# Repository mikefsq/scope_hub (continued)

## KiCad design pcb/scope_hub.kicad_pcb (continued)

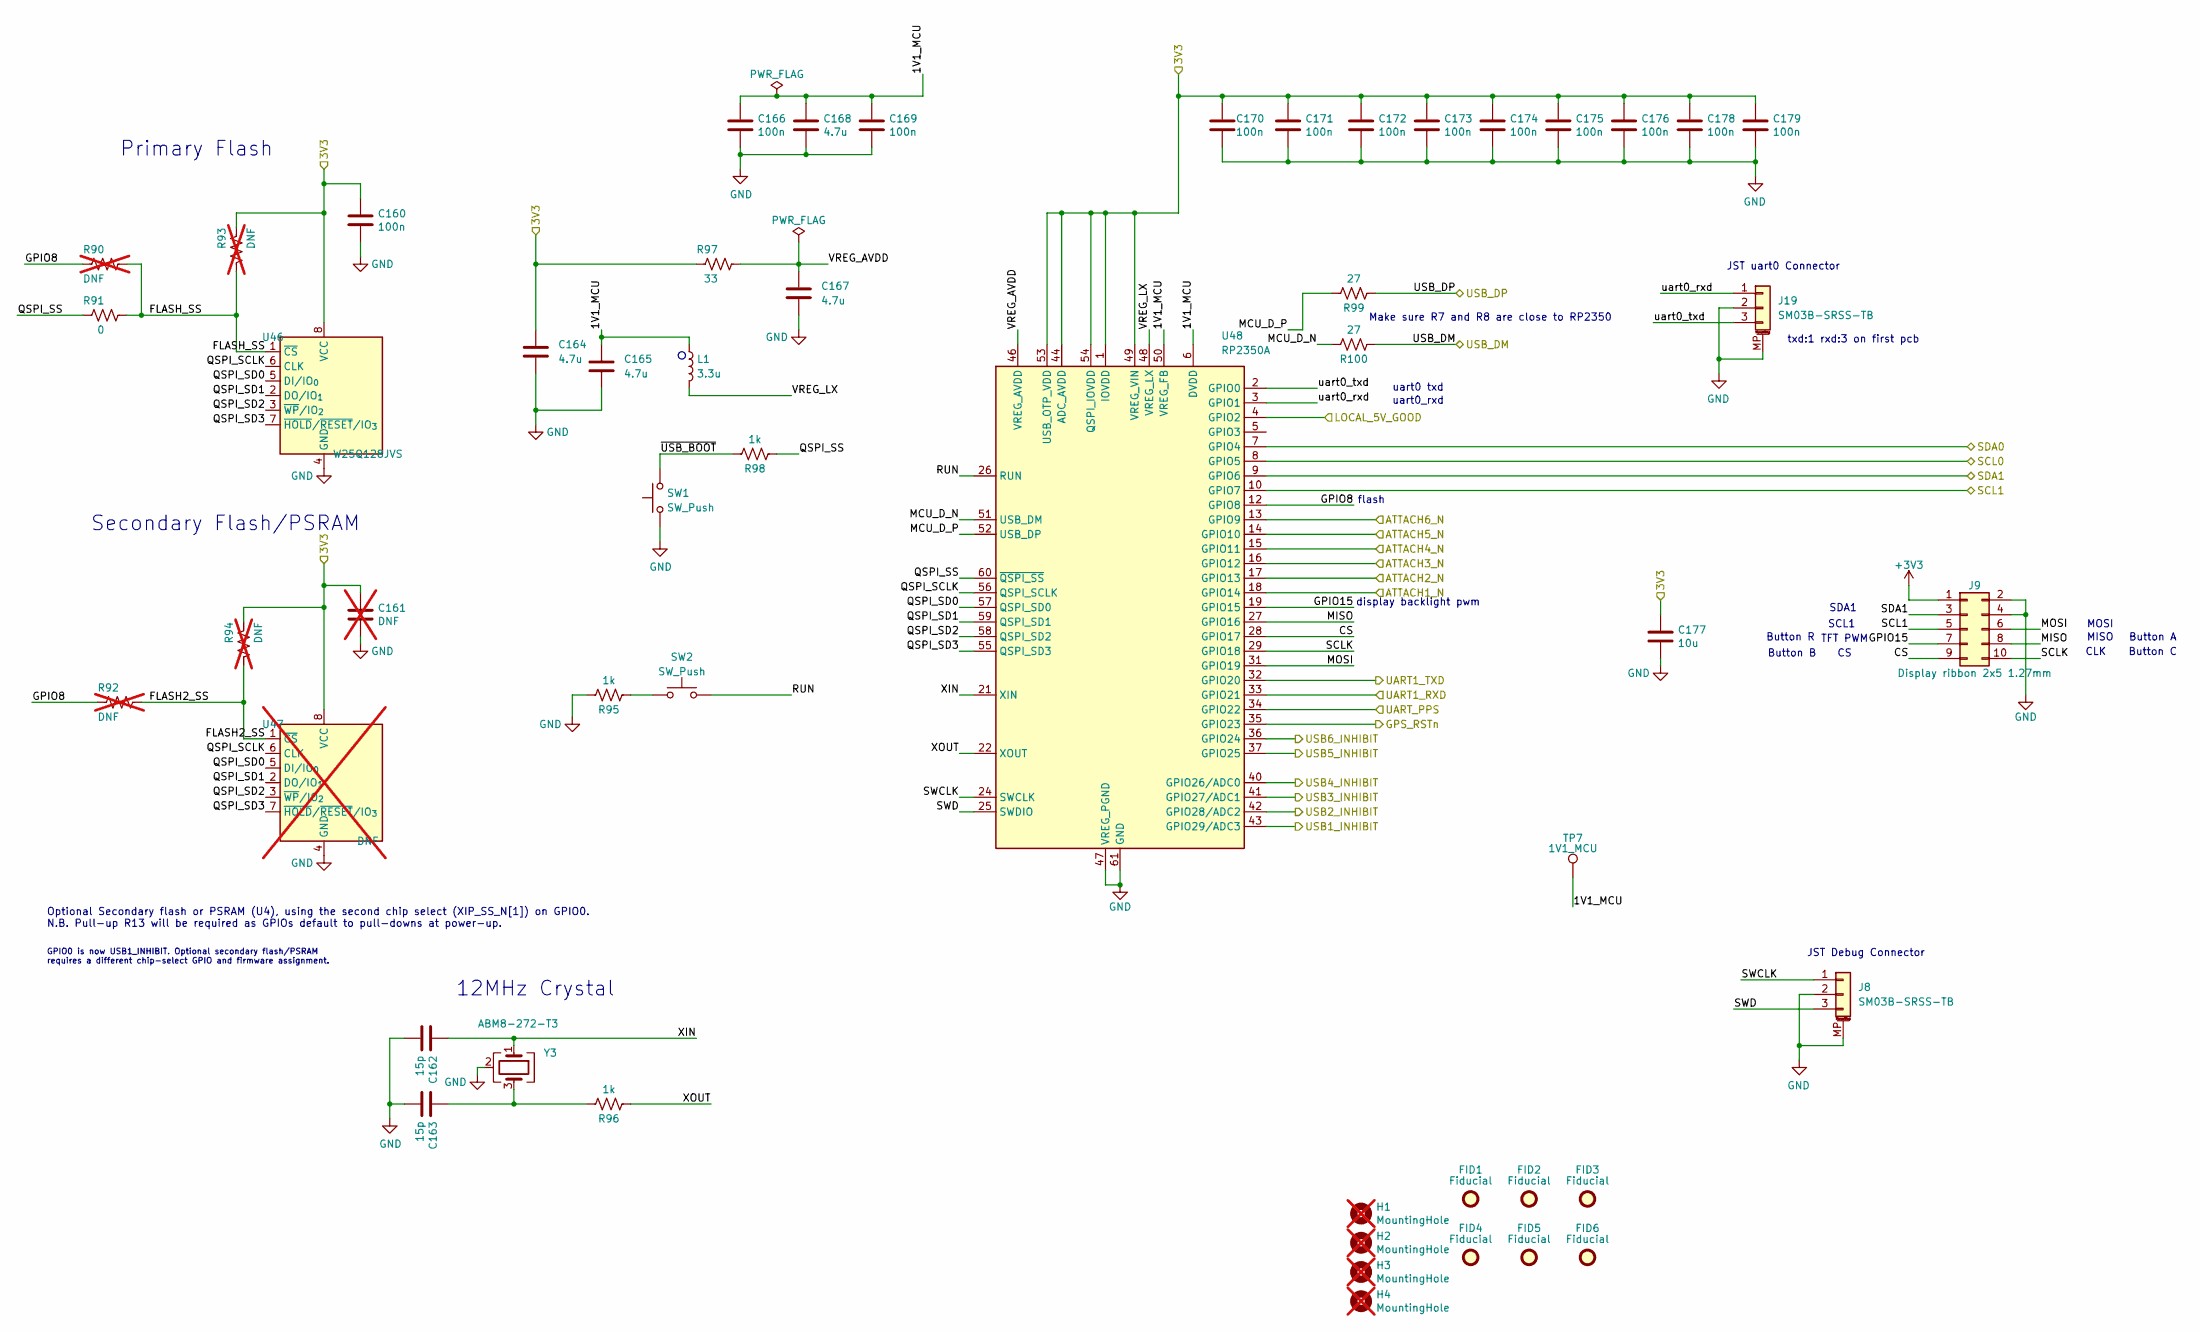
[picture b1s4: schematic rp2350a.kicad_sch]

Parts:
C160, C166, C169, C170, C171, C172, C173, C174, C175, C176, C178, C179: 100n; C_0402_1005Metric; LCSC C1525
C161: DNF; C_0402_1005Metric; not fitted
C162, C163: 15p; C_0402_1005Metric; LCSC C1548
C164, C165, C167, C168: 4.7u; C_0402_1005Metric; LCSC C23733
C177: 10u; C_0805_2012Metric; LCSC C15850
FID1, FID2, FID3, FID4, FID5, FID6: Fiducial; Fiducial_1mm_Mask3mm
H1, H2, H3, H4: MountingHole; MountingHole_3.2mm_M3; not fitted
J8, J19: SM03B-SRSS-TB; JST_SH_SM03B-SRSS-TB_1x03-1MP_P1.00mm_Horizontal; MPN SM03B-SRSS-TB(LF)(SN); LCSC C160403
J9: Display ribbon 2x5 1.27mm; PinHeader_2x05_P1.27mm_Vertical_SMD; MPN FTSH-105-01-L-DV-K-TR; LCSC C448647
L1: 3.3u; L_pol_2016; MPN AOTA-B201610S3R3-101-T; LCSC C42411119
R90, R92, R93, R94: DNF; R_0402_1005Metric; not fitted
R91: 0; R_0402_1005Metric; LCSC C17168
R95, R96, R98: 1k; R_0402_1005Metric; LCSC C11702
R97: 33; R_0402_1005Metric; LCSC C25105
R99, R100: 27; R_0402_1005Metric; LCSC C25100
SW1, SW2: SW_Push; SW_Push_1P1T_NO_Vertical_Wuerth_434133025816; MPN 434133025816; LCSC C5504987
TP7: 1V1_MCU; TestPoint_Pad_D1.5mm
U46: W25Q128JVS; SOIC-8_5.3x5.3mm_P1.27mm; MPN W25Q128JVSIQ; LCSC C97521
U47: DNF; SOIC-8_5.3x5.3mm_P1.27mm; not fitted
U48: RP2350A; QFN-60-1EP_7x7mm_P0.4mm_EP3.4x3.4mm_ThermalVias; LCSC C42411118
Y3: ABM8-272-T3; Crystal_SMD_3225-4Pin_3.2x2.5mm; MPN ABM8-272-T3; LCSC C20625731

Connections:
+3V3: C160.1, C161.1, C164.1, C170.1, C171.1, C172.1, C173.1, C174.1, C175.1, C176.1, C177.1, C178.1, C179.1, J9.1, R93.1, R94.1, R97.1, U46.8 (VCC), U47.8 (VCC), U48.1 (IOVDD), U48.11 (IOVDD), U48.20 (IOVDD), U48.30 (IOVDD), U48.38 (IOVDD), U48.44 (ADC_AVDD), U48.45 (IOVDD), U48.49 (VREG_VIN), U48.53 (USB_OTP_VDD), U48.54 (QSPI_IOVDD); also elsewhere on the board
/ATTACH1_N: U48.18 (GPIO14); also elsewhere on the board
/ATTACH2_N: U48.17 (GPIO13); also elsewhere on the board
/ATTACH3_N: U48.16 (GPIO12); also elsewhere on the board
/ATTACH4_N: U48.15 (GPIO11); also elsewhere on the board
/ATTACH5_N: U48.14 (GPIO10); also elsewhere on the board
/ATTACH6_N: U48.13 (GPIO9); also elsewhere on the board
/GPS_PPS: U48.34 (GPIO22); also elsewhere on the board
/GPS_RSTn: U48.35 (GPIO23); also elsewhere on the board
/GPS_RXD: U48.32 (GPIO20); also elsewhere on the board
/GPS_TXD: U48.33 (GPIO21); also elsewhere on the board
/I2C0_SCL: U48.8 (GPIO5); also elsewhere on the board
/I2C0_SDA: U48.7 (GPIO4); also elsewhere on the board
/I2C1_SCL: J9.5, U48.10 (GPIO7); also elsewhere on the board
/I2C1_SDA: J9.3, U48.9 (GPIO6); also elsewhere on the board
/LOCAL_5V_GOOD: U48.4 (GPIO2); also elsewhere on the board
/PICO_D_N: R100.1; also elsewhere on the board
/PICO_D_P: R99.1; also elsewhere on the board
/RP2350A/1V1_MCU: C165.1, C166.1, C168.1, C169.1, L1.1, TP7.1 (1_1), U48.6 (DVDD), U48.23 (DVDD), U48.39 (DVDD), U48.50 (VREG_FB)
/RP2350A/CS: J9.9, U48.28 (GPIO17)
/RP2350A/FLASH2_SS: R92.2, R94.2, U47.1 (~CS)
/RP2350A/FLASH_SS: R90.2, R91.2, R93.2, U46.1 (~CS)
/RP2350A/GPIO8: R90.1, R92.1, U48.12 (GPIO8)
/RP2350A/GPIO15: J9.7, U48.19 (GPIO15)
/RP2350A/MCU_D_N: R100.2, U48.51 (USB_DM)
/RP2350A/MCU_D_P: R99.2, U48.52 (USB_DP)
/RP2350A/MISO: J9.8, U48.27 (GPIO16)
/RP2350A/MOSI: J9.6, U48.31 (GPIO19)
/RP2350A/QSPI_SCLK: U46.6 (CLK), U47.6 (CLK), U48.56 (QSPI_SCLK)
/RP2350A/QSPI_SD0: U46.5 (DI/IO_{0}), U47.5 (DI/IO_{0}), U48.57 (QSPI_SD0)
/RP2350A/QSPI_SD1: U46.2 (DO/IO_{1}), U47.2 (DO/IO_{1}), U48.59 (QSPI_SD1)
/RP2350A/QSPI_SD2: U46.3 (~WP/IO_{2}), U47.3 (~WP/IO_{2}), U48.58 (QSPI_SD2)
/RP2350A/QSPI_SD3: U46.7 (~HOLD/~RESET/IO_{3}), U47.7 (~HOLD/~RESET/IO_{3}), U48.55 (QSPI_SD3)
/RP2350A/QSPI_SS: R91.1, R98.1, U48.60 (~QSPI_SS)
/RP2350A/RUN: SW2.2, U48.26 (RUN)
/RP2350A/SCLK: J9.10, U48.29 (GPIO18)
/RP2350A/SWCLK: J8.1, U48.24 (SWCLK)
/RP2350A/SWD: J8.3, U48.25 (SWDIO)
/RP2350A/VREG_AVDD: C167.1, R97.2, U48.46 (VREG_AVDD)
/RP2350A/VREG_LX: L1.2, U48.48 (VREG_LX)
/RP2350A/XIN: C162.1, U48.21 (XIN), Y3.1
/RP2350A/XOUT: R96.1, U48.22 (XOUT)
/RP2350A/uart0_rxd: J19.1, U48.3 (GPIO1)
/RP2350A/uart0_txd: J19.3, U48.2 (GPIO0)
/RP2350A/~USB_BOOT: R98.2, SW1.2
/USB1_INHIBIT: U48.43 (GPIO29/ADC3); also elsewhere on the board
/USB2_INHIBIT: U48.42 (GPIO28/ADC2); also elsewhere on the board
/USB3_INHIBIT: U48.41 (GPIO27/ADC1); also elsewhere on the board
/USB4_INHIBIT: U48.40 (GPIO26/ADC0); also elsewhere on the board
/USB5_INHIBIT: U48.37 (GPIO25); also elsewhere on the board
/USB6_INHIBIT: U48.36 (GPIO24); also elsewhere on the board
GND: C160.2, C161.2, C162.2, C163.2, C164.2, C165.2, C166.2, C167.2, C168.2, C169.2, C170.2, C171.2, C172.2, C173.2, C174.2, C175.2, C176.2, C177.2, C178.2, C179.2, J8.2, J8.MP (MountPin), J9.2, J9.4, J19.2, J19.MP (MountPin), R95.2, SW1.1, U46.4 (GND), U47.4 (GND), U48.47 (VREG_PGND), U48.61 (GND), Y3.2 (G), Y3.4 (G); also elsewhere on the board
unnamed: C163.1, R96.2, Y3.3
unnamed: R95.1, SW2.1

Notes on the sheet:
Button A
display backlight pwm
Secondary Flash/PSRAM
JST Debug Connector
12MHz Crystal
GPIO0 is now USB1_INHIBIT. Optional secondary flash/PSRAM requires a different chip-select GPIO and firmware assignment.
MOSI
uart0_rxd
SCL1
uart0 txd
Optional Secondary flash or PSRAM (U4), using the second chip select (XIP_SS_N[1]) on GPIO0. N.B. Pull-up R13 will be required as GPIOs default to pull-downs at power-up.
flash
MISO
Button R
TFT PWM
txd:1 rxd:3 on first pcb
SDA1
JST uart0 Connector
Button C
Make sure R7 and R8 are close to RP2350
CLK
Button B
Primary Flash

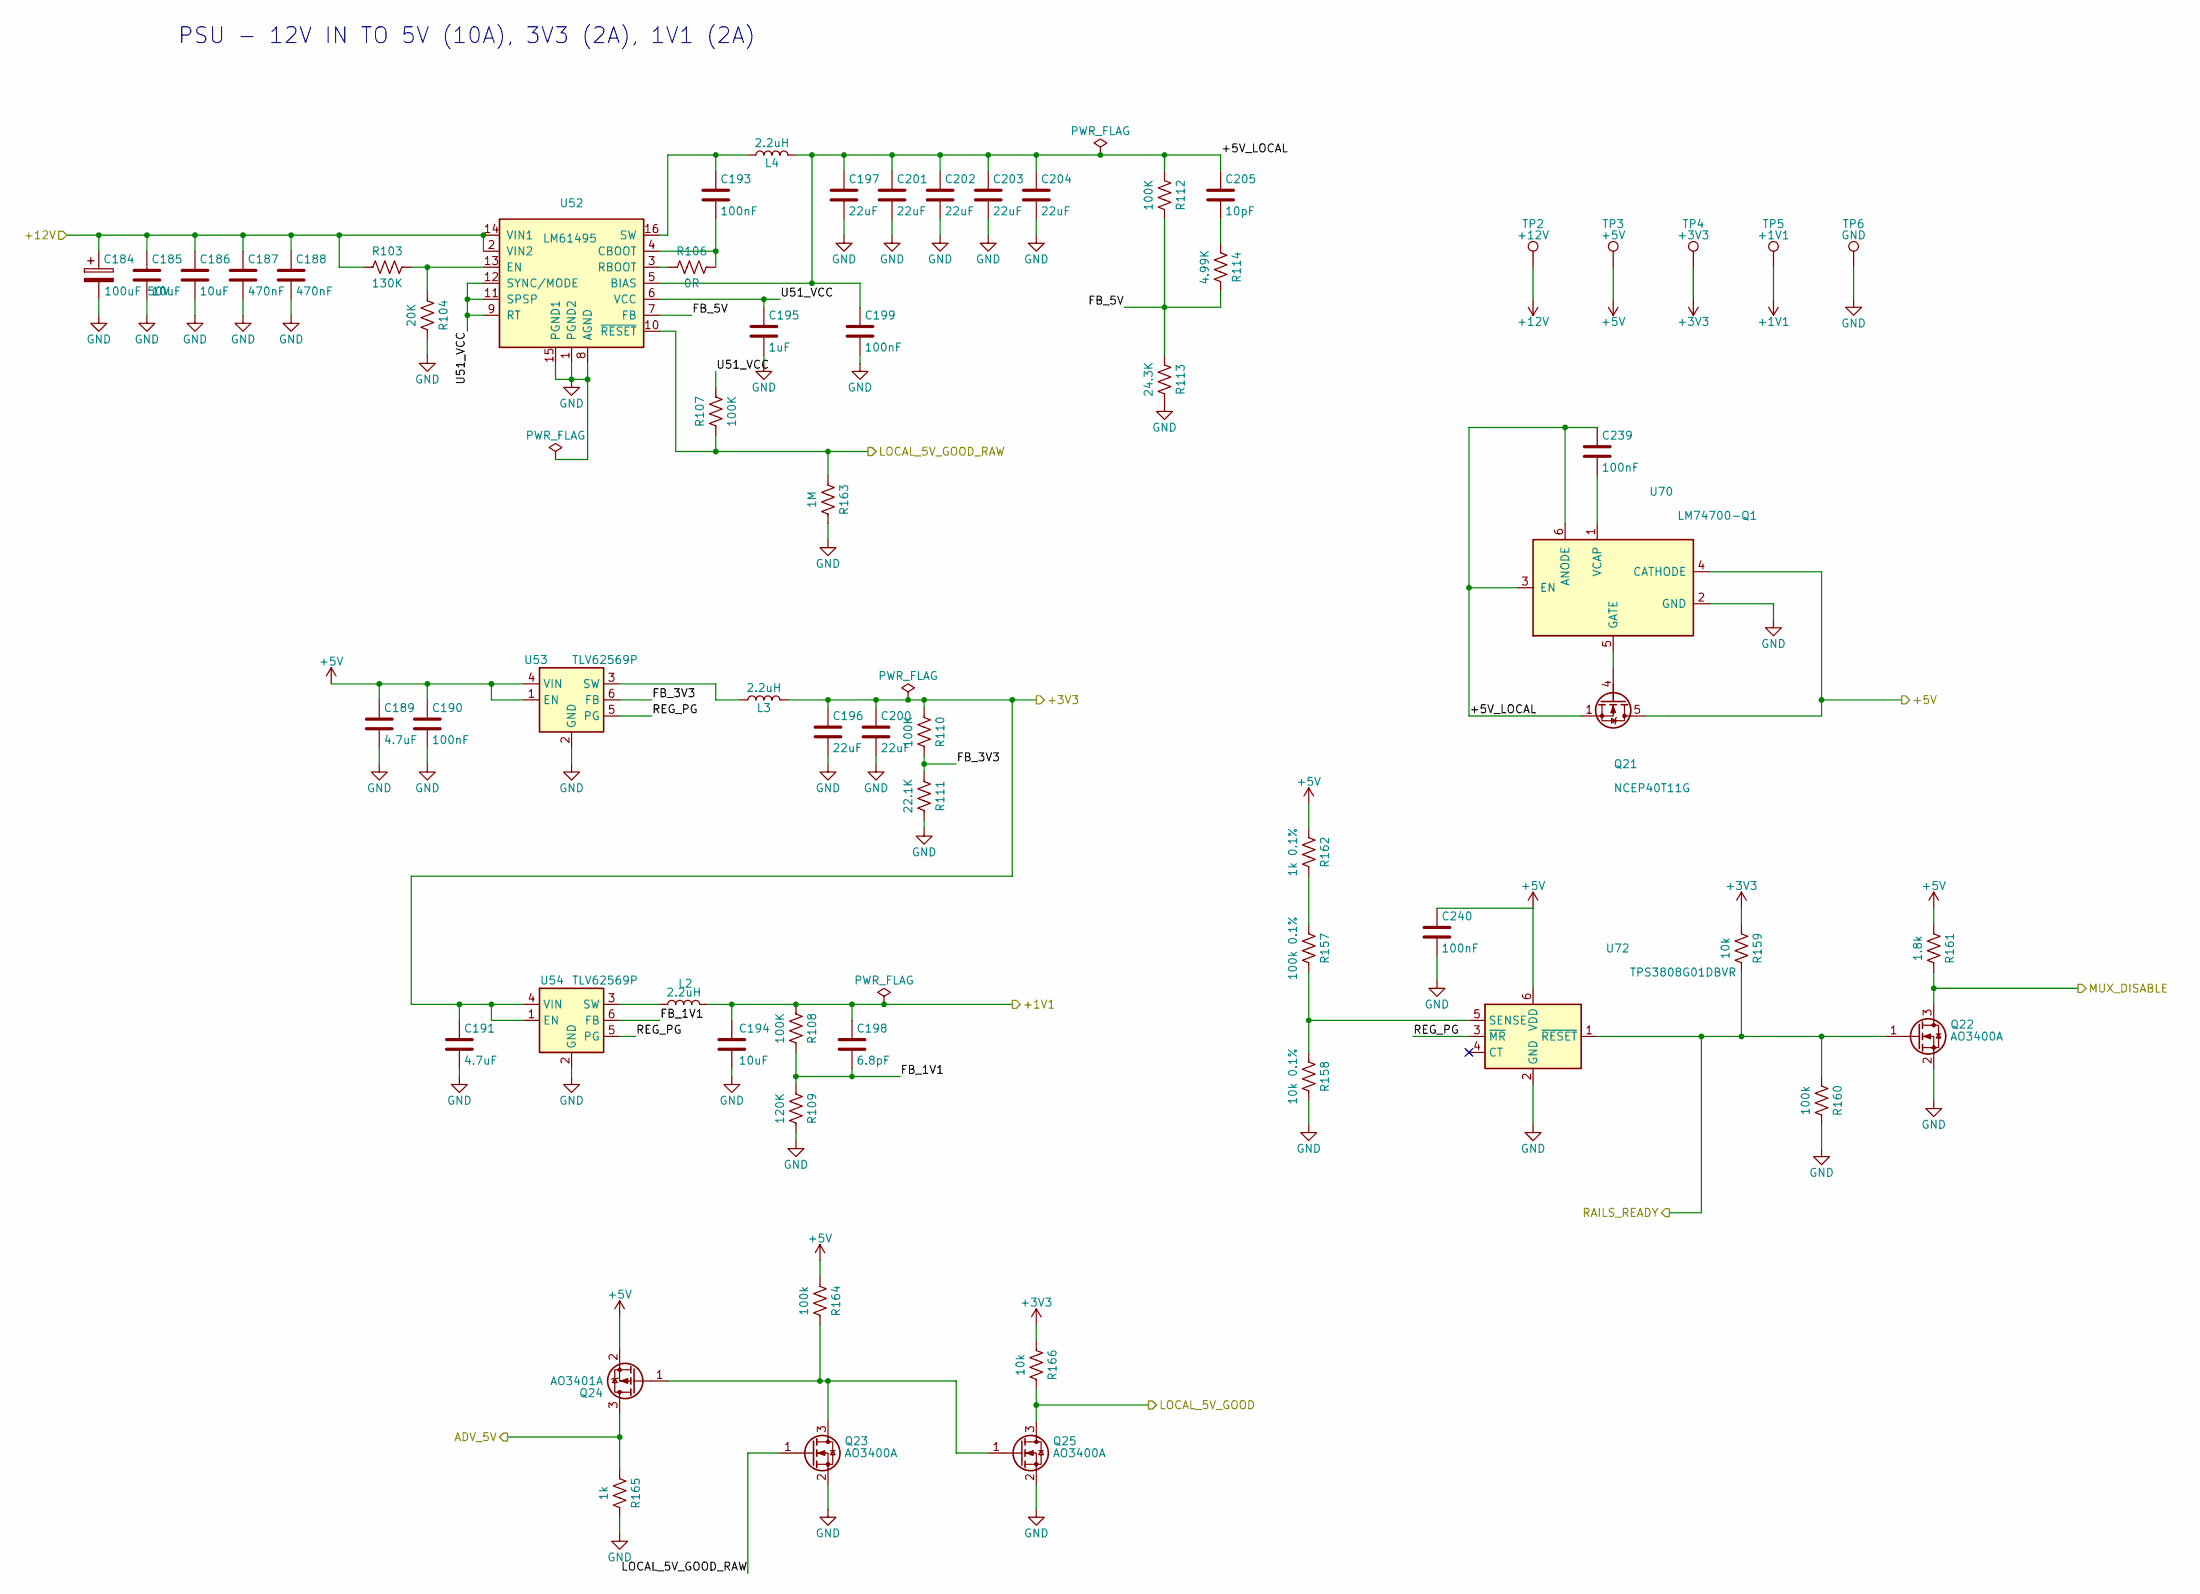
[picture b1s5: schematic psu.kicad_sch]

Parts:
C184: 100uF 50V; CP_Elec_6.3x7.7; LCSC C2980173
C185, C186: 10uF; C_1210_3225Metric; LCSC C386166
C187, C188: 470nF; C_0603_1608Metric; LCSC C513577
C189: 4.7uF; C_1206_3216Metric; LCSC C51205
C190: 100nF; C_0603_1608Metric; LCSC C14663
C191: 4.7uF; C_0805_2012Metric; LCSC C354262
C193, C199, C240: 100nF; C_0402_1005Metric; LCSC C1525
C194: 10uF; C_0805_2012Metric; LCSC C15850
C195: 1uF; C_0603_1608Metric; LCSC C5199872
C196, C200: 22uF; C_0805_2012Metric; LCSC C98190
C197, C201, C202, C203, C204: 22uF; C_1210_3225Metric; LCSC C309062
C198: 6.8pF; C_0402_1005Metric; LCSC C189470
C205: 10pF; C_0402_1005Metric; LCSC C106199
C239: 100nF; C_0603_1608Metric; Voltage 50V; MPN CC0603KRX7R9BB104; LCSC C14663
L2: 2.2uH; L_Sunlord_SWPA4020S; LCSC C83423
L3: 2.2uH; L_Sunlord_SWPA4020S; MPN SWPA4020S2R2MT; LCSC C83423
L4: 2.2uH; L_Changjiang_FXL1040; LCSC C167228
Q21: NCEP40T11G; PowerPAK_SO-8_Single; MPN NCEP40T11G; LCSC C182465
Q22, Q23, Q25: AO3400A; SOT-23; MPN AO3400A; LCSC C20917
Q24: AO3401A; SOT-23; MPN AO3401A; LCSC C15127
R103: 130K; R_0402_1005Metric; LCSC C93946
R104: 20K; R_0402_1005Metric; LCSC C25765
R106: 0R; R_0402_1005Metric; LCSC C2906858
R107, R108, R110, R112: 100K; R_0402_1005Metric; LCSC C25741
R109: 120K; R_0402_1005Metric; LCSC C25750
R111: 22.1K; R_0402_1005Metric; LCSC C163478
R113: 24.3K; R_0402_1005Metric; LCSC C26969
R114: 4.99K; R_0402_1005Metric; LCSC C2933102
R157: 100k 0.1%; R_0402_1005Metric; Tolerance 0.1%; MPN RT0402BRD07100KL; LCSC C852472
R158: 10k 0.1%; R_0402_1005Metric; Tolerance 0.1%; MPN RT0402BRD0710KL; LCSC C190095
R159: 10k; R_0402_1005Metric; Tolerance 1%; LCSC C25744
R160: 100k; R_0402_1005Metric; Tolerance 1%; LCSC C25741
R161: 1.8k; R_0402_1005Metric; Tolerance 1%; MPN RC0402FR-071K8L; LCSC C163481
R162: 1k 0.1%; R_0402_1005Metric; Tolerance 0.1%; MPN RT0402BRD071KL; LCSC C852624
R163: 1M; R_0402_1005Metric; LCSC C26083
R164: 100k; R_0402_1005Metric; LCSC C25741
R165: 1k; R_0402_1005Metric; LCSC C11702
R166: 10k; R_0402_1005Metric; LCSC C25744
TP2: +12V; TestPoint_Pad_D1.5mm
TP3: +5V; TestPoint_Pad_D1.5mm
TP4: +3V3; TestPoint_Pad_D1.5mm
TP5: +1V1; TestPoint_Pad_D1.5mm
TP6: GND; TestPoint_Pad_D1.5mm
U52: LM61495; Texas_RPH0016A_VQFN-HR-16_3.5x4.5mm; MPN LM61495RPHR; LCSC C2943584
U53, U54: TLV62569P; TSOT-23-6; MPN TLV62569PDDCR; LCSC C398365
U70: LM74700-Q1; SOT-23-6; MPN LM74700QDBVRQ1; LCSC C2941042
U72: TPS3808G01DBVR; SOT-23-6; MPN TPS3808G01DBVR; LCSC C19653

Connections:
+1V1: C194.1, C198.1, L2.2, R108.1, TP5.1 (1_1); also elsewhere on the board
+3V3: C191.1, C196.1, C200.1, L3.2, R110.1, R159.1, R166.1, TP4.1 (1_1), U54.1 (EN), U54.4 (VIN); also elsewhere on the board
+5V: C189.1, C190.1, C240.1, Q21.5 (D), Q24.2 (S), R161.1, R162.1, R164.1, TP3.1 (1_1), U53.1 (EN), U53.4 (VIN), U70.4 (CATHODE), U72.6 (VDD); also elsewhere on the board
+12V: C184.1, C185.1, C186.1, C187.1, C188.1, R103.1, TP2.1 (1_1), U52.2 (VIN2), U52.14 (VIN1); also elsewhere on the board
/ADV_5V: Q24.3 (D), R165.1; also elsewhere on the board
/LOCAL_5V_GOOD: Q25.3 (D), R166.2; also elsewhere on the board
/LOCAL_5V_GOOD_RAW: Q23.1 (G), R107.1, R163.1, U52.10 (~RESET); also elsewhere on the board
/MUX_DISABLE: Q22.3 (D), R161.2; also elsewhere on the board
/PSU 12V to 5V/3V3/1V1/+5V_LOCAL: C197.1, C199.1, C201.1, C202.1, C203.1, C204.1, C205.1, C239.1, L4.2, Q21.1 (S), Q21.2 (S), Q21.3 (S), R112.1, U52.5 (BIAS), U70.3 (EN), U70.6 (ANODE)
/PSU 12V to 5V/3V3/1V1/FB_1V1: C198.2, R108.2, R109.1, U54.6 (FB)
/PSU 12V to 5V/3V3/1V1/FB_3V3: R110.2, R111.1, U53.6 (FB)
/PSU 12V to 5V/3V3/1V1/FB_5V: R112.2, R113.1, R114.2, U52.7 (FB)
/PSU 12V to 5V/3V3/1V1/REG_PG: U53.5 (PG), U54.5 (PG), U72.3 (~MR)
/PSU 12V to 5V/3V3/1V1/U51_VCC: C195.1, R107.2, U52.6 (VCC), U52.9 (RT), U52.11 (SPSP), U52.12 (SYNC/MODE)
/RAILS_READY: Q22.1 (G), R159.2, R160.1, U72.1 (~RESET); also elsewhere on the board
GND: C184.2, C185.2, C186.2, C187.2, C188.2, C189.2, C190.2, C191.2, C194.2, C195.2, C196.2, C197.2, C199.2, C200.2, C201.2, C202.2, C203.2, C204.2, C240.2, Q22.2 (S), Q23.2 (S), Q25.2 (S), R104.2, R109.2, R111.2, R113.2, R158.2, R160.2, R163.2, R165.2, TP6.1 (1_1), U52.1 (PGND2), U52.8 (AGND), U52.15 (PGND1), U53.2 (GND), U54.2 (GND), U70.2 (GND), U72.2 (GND); also elsewhere on the board
unnamed: C205.2, R114.1
unnamed: Q21.4 (G), U70.5 (GATE)
unnamed: Q23.3 (D), Q24.1 (G), Q25.1 (G), R164.2
unnamed: R157.1, R162.2
unnamed: C193.2, R106.2, U52.4 (CBOOT)
unnamed: R103.2, R104.1, U52.13 (EN)
unnamed: R106.1, U52.3 (RBOOT)
unnamed: C193.1, L4.1, U52.16 (SW)
unnamed: L3.1, U53.3 (SW)
unnamed: L2.1, U54.3 (SW)
unnamed: C239.2, U70.1 (VCAP)
unnamed: R157.2, R158.1, U72.5 (SENSE)

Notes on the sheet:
PSU - 12V IN TO 5V (10A), 3V3 (2A), 1V1 (2A)

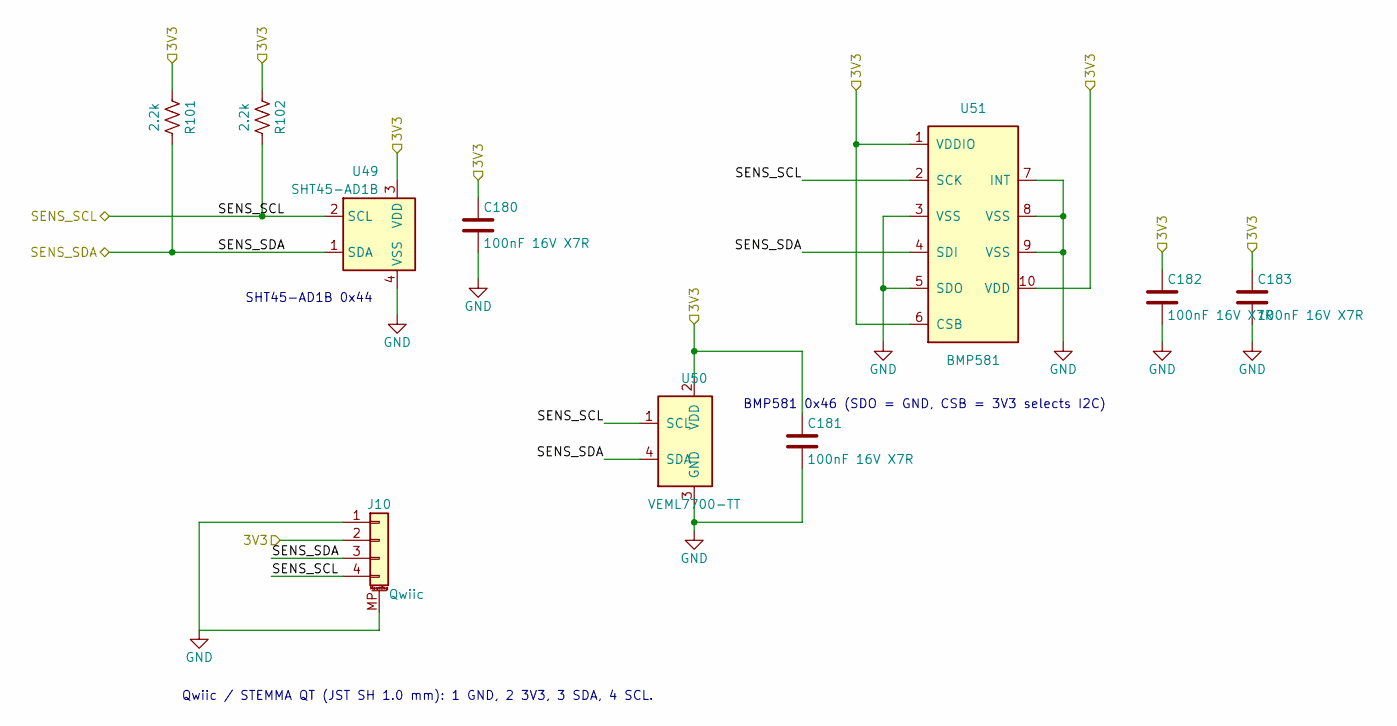
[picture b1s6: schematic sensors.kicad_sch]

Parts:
C180, C181, C182, C183: 100nF 16V X7R; C_0402_1005Metric; LCSC C1525
J10: Qwiic; JST_SH_SM04B-SRSS-TB_1x04-1MP_P1.00mm_Horizontal; LCSC C160404
R101, R102: 2.2k; R_0402_1005Metric; LCSC C25879
U49: SHT45-AD1B; Sensirion_DFN-4_1.5x1.5mm_P0.8mm_SHT4x_NoCentralPad; LCSC C5221601
U50: VEML7700-TT; Vishay_VEML7700-TT; MPN VEML7700-TT; LCSC C1850416
U51: BMP581; Bosch_LGA-10_2x2mm_P0.5mm_BMP581; LCSC C5362283

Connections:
+3V3: C180.1, C181.1, C182.1, C183.1, J10.2, R101.1, R102.1, U49.3 (VDD), U50.2 (VDD), U51.1 (VDDIO), U51.6 (CSB), U51.10 (VDD); also elsewhere on the board
/I2C1_SCL: J10.4, R102.2, U49.2 (SCL), U50.1 (SCL), U51.2 (SCK); also elsewhere on the board
/I2C1_SDA: J10.3, R101.2, U49.1 (SDA), U50.4 (SDA), U51.4 (SDI); also elsewhere on the board
GND: C180.2, C181.2, C182.2, C183.2, J10.1, J10.MP (MountPin), U49.4 (VSS), U50.3 (GND), U51.3 (VSS), U51.5 (SDO), U51.7 (INT), U51.8 (VSS), U51.9 (VSS); also elsewhere on the board

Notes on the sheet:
BMP581 0x46 (SDO = GND, CSB = 3V3 selects I2C)
Qwiic / STEMMA QT (JST SH 1.0 mm): 1 GND, 2 3V3, 3 SDA, 4 SCL.
SHT45-AD1B 0x44

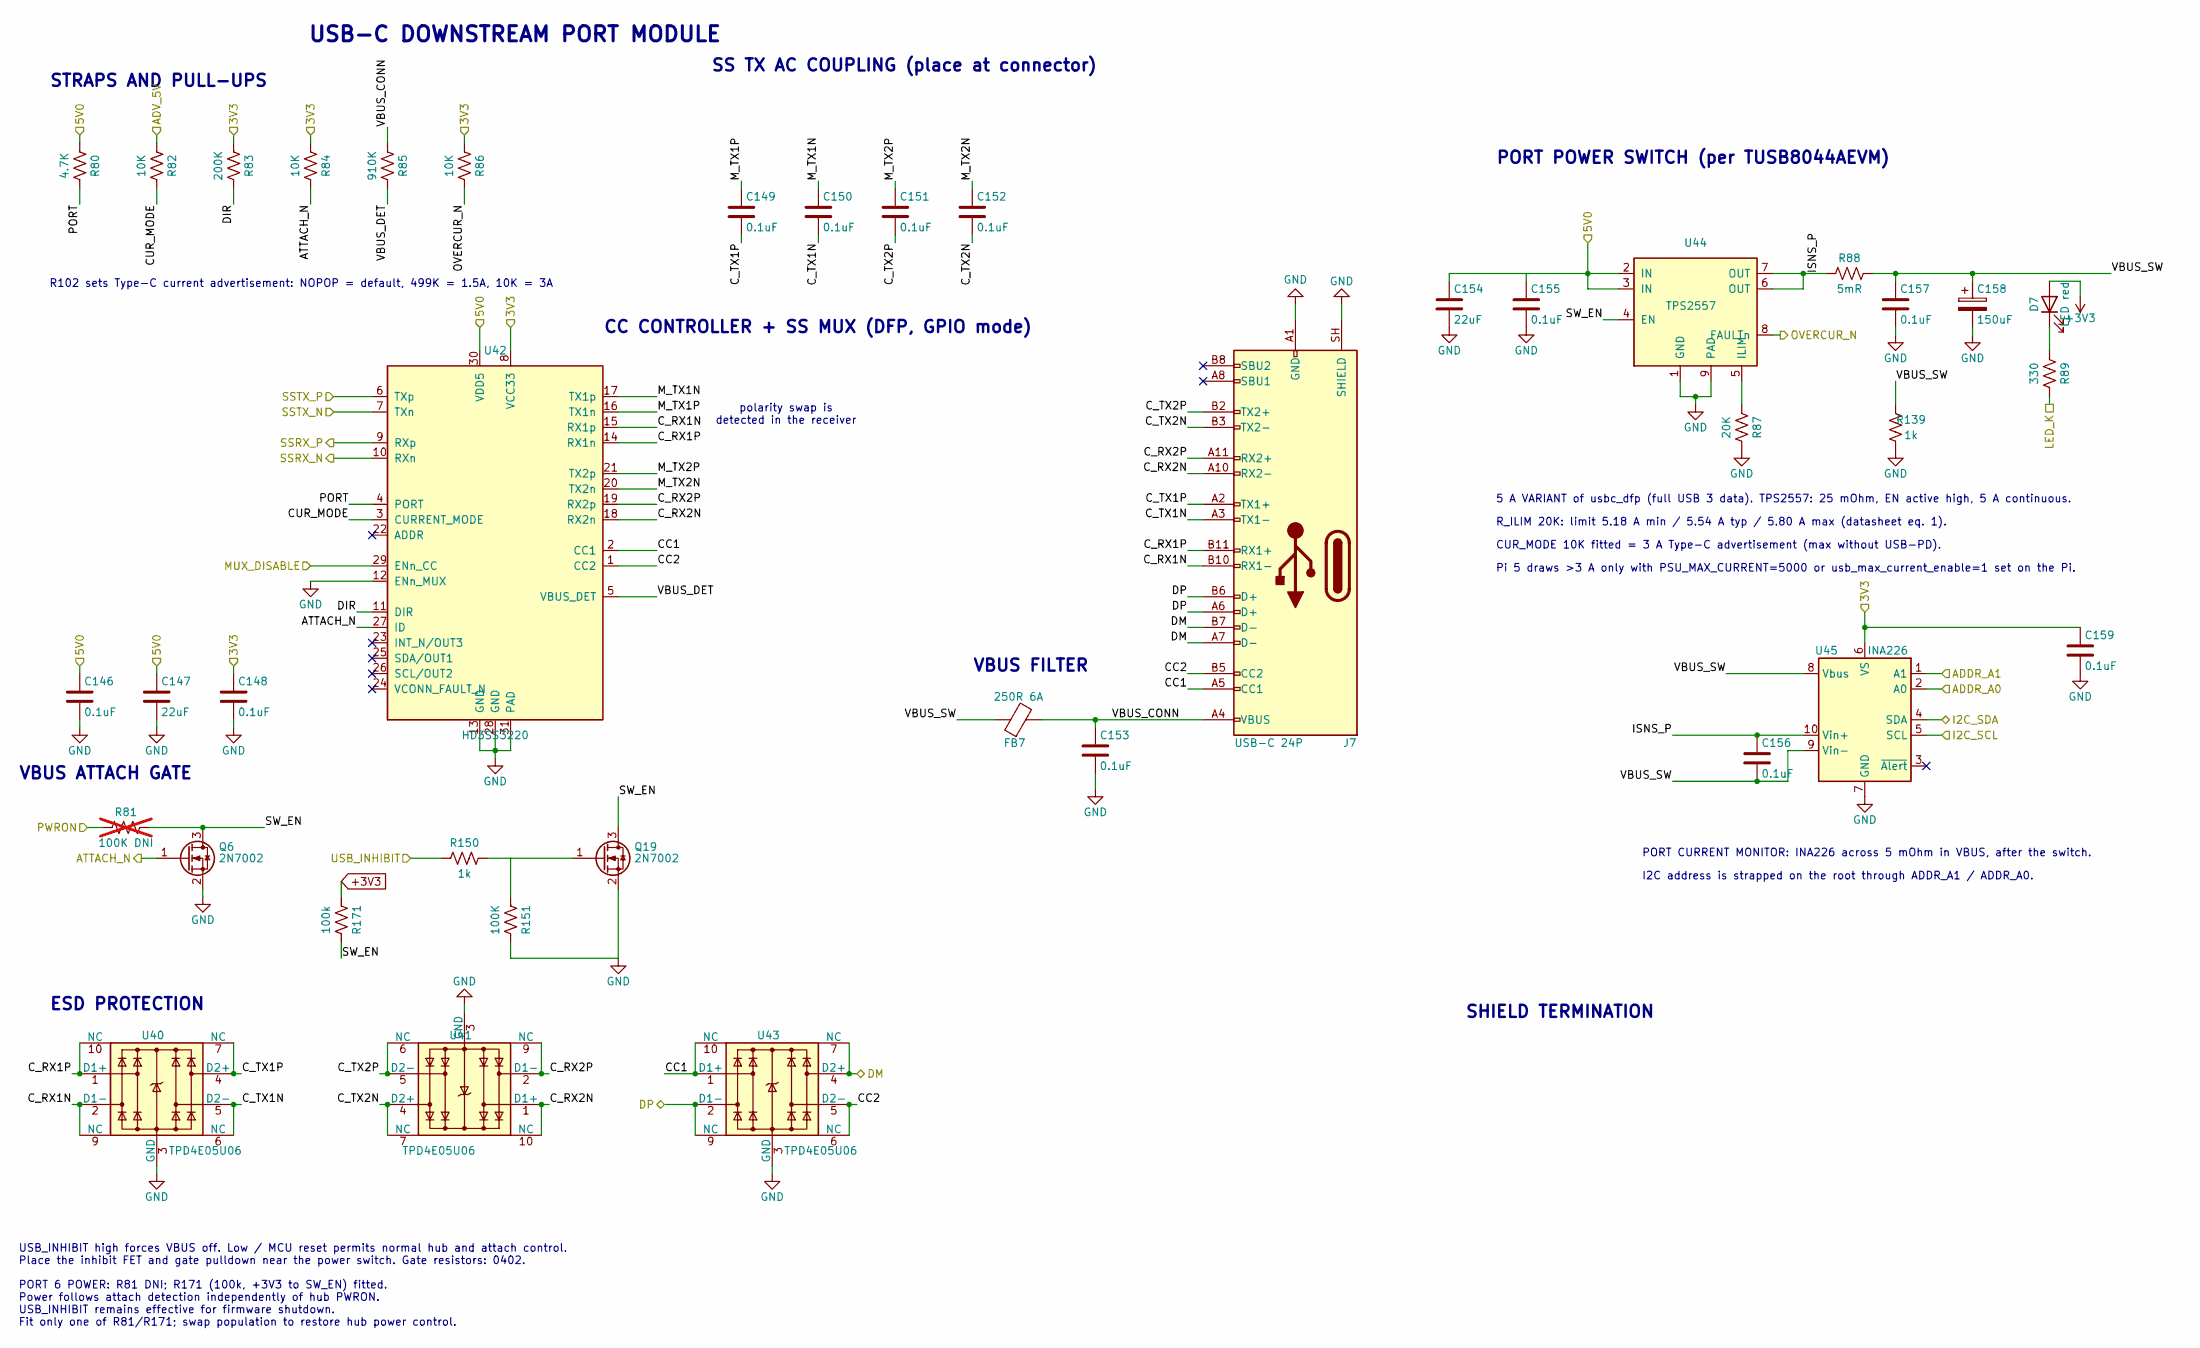
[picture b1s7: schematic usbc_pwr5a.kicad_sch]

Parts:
C146, C148, C149, C150, C151, C152, C153, C155, C156, C157, C159: 0.1uF; C_0402_1005Metric; LCSC C1525
C147, C154: 22uF; C_0805_2012Metric; LCSC C45783
C158: 150uF; CP_EIA-3528-21_Kemet-B; LCSC C212682
D7: LED red; LED_0805_2012Metric; LCSC C84256
FB7: 250R 6A; FB_201210_PROD; MPN PSBHAA201210H-251T060; LCSC C48543401
J7: USB-C 24P; USB_C_Receptacle_Molex_105450-0101; MPN 105450-0101; LCSC C134092
Q6: 2N7002; SOT-23; LCSC C8545
Q19: 2N7002; SOT-23; MPN 2N7002; LCSC C8545
R80: 4.7K; R_0402_1005Metric; LCSC C25900
R81: 100K DNI; R_0402_1005Metric; LCSC C25741; not fitted
R82, R84, R86: 10K; R_0402_1005Metric; LCSC C25744
R83: 200K; R_0402_1005Metric; LCSC C25764
R85: 910K; R_0402_1005Metric; LCSC C25800
R87: 20K; R_0402_1005Metric; LCSC C25765
R88: 5mR; R_1206_3216Metric; LCSC C7419996
R89: 330; R_0402_1005Metric; LCSC C25104
R139: 1k; R_0402_1005Metric; MPN 0402WGF1001TCE; LCSC C11702
R150: 1k; R_0402_1005Metric; LCSC C11702
R151: 100K; R_0402_1005Metric; LCSC C25741
R171: 100k; R_0402_1005Metric; LCSC C25741
U40, U41, U43: TPD4E05U06; USON-10_2.5x1.0mm_P0.5mm; LCSC C138714
U42: HD3SS3220; Texas_RNH0030A_WQFN-30-1EP_2.5x4.5mm_P0.4mm_EP1.2x3.2mm; LCSC C165155
U44: TPS2557; VSON-8-1EP_3x3mm_P0.65mm_EP1.65x2.4mm; LCSC C130056
U45: INA226; TSSOP-10_3x3mm_P0.5mm; MPN INA226AIDGSR; LCSC C49851

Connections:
+3V3: C148.1, C159.1, D7.2 (A), R83.1, R84.1, R86.1, R171.1, U42.8 (VCC33), U45.6 (VS); also elsewhere on the board
+5V: C146.1, C147.1, C154.1, C155.1, R80.1, U42.30 (VDD5), U44.2 (IN), U44.3 (IN); also elsewhere on the board
/ADV_5V: R82.1; also elsewhere on the board
/ATTACH6_N: Q6.1 (G), R84.2, U42.27 (ID); also elsewhere on the board
/DN6_D_N: J7.A7 (D-), J7.B7 (D-), U43.4 (D2+), U43.7 (NC); also elsewhere on the board
/DN6_D_P: J7.A6 (D+), J7.B6 (D+), U43.2 (D1-), U43.9 (NC); also elsewhere on the board
/DN Port 6 (5A)/CC1: J7.A5 (CC1), U42.2 (CC1), U43.1 (D1+), U43.10 (NC)
/DN Port 6 (5A)/CC2: J7.B5 (CC2), U42.1 (CC2), U43.5 (D2-), U43.6 (NC)
/DN Port 6 (5A)/CUR_MODE: R82.2, U42.3 (CURRENT_MODE)
/DN Port 6 (5A)/C_RX1N: J7.B10 (RX1-), U40.2 (D1-), U40.9 (NC), U42.15 (RX1p)
/DN Port 6 (5A)/C_RX1P: J7.B11 (RX1+), U40.1 (D1+), U40.10 (NC), U42.14 (RX1n)
/DN Port 6 (5A)/C_RX2N: J7.A10 (RX2-), U41.1 (D1+), U41.10 (NC), U42.18 (RX2n)
/DN Port 6 (5A)/C_RX2P: J7.A11 (RX2+), U41.2 (D1-), U41.9 (NC), U42.19 (RX2p)
/DN Port 6 (5A)/C_TX1N: C150.2, J7.A3 (TX1-), U40.5 (D2-), U40.6 (NC)
/DN Port 6 (5A)/C_TX1P: C149.2, J7.A2 (TX1+), U40.4 (D2+), U40.7 (NC)
/DN Port 6 (5A)/C_TX2N: C152.2, J7.B3 (TX2-), U41.4 (D2+), U41.7 (NC)
/DN Port 6 (5A)/C_TX2P: C151.2, J7.B2 (TX2+), U41.5 (D2-), U41.6 (NC)
/DN Port 6 (5A)/DIR: R83.2, U42.11 (DIR)
/DN Port 6 (5A)/ISNS_P: C156.1, R88.1, U44.6 (OUT), U44.7 (OUT), U45.10 (Vin+)
/DN Port 6 (5A)/M_TX1N: C150.1, U42.17 (TX1p)
/DN Port 6 (5A)/M_TX1P: C149.1, U42.16 (TX1n)
/DN Port 6 (5A)/M_TX2N: C152.1, U42.20 (TX2n)
/DN Port 6 (5A)/M_TX2P: C151.1, U42.21 (TX2p)
/DN Port 6 (5A)/OVERCUR_N: R86.2, U44.8 (FAULTn); also elsewhere on the board
/DN Port 6 (5A)/PORT: R80.2, U42.4 (PORT)
/DN Port 6 (5A)/SSRX_N: U42.10 (RXn); also elsewhere on the board
/DN Port 6 (5A)/SSRX_P: U42.9 (RXp); also elsewhere on the board
/DN Port 6 (5A)/SSTX_N: U42.7 (TXn); also elsewhere on the board
/DN Port 6 (5A)/SSTX_P: U42.6 (TXp); also elsewhere on the board
/DN Port 6 (5A)/SW_EN: Q6.3 (D), Q19.3 (D), R81.2, R171.2, U44.4 (EN)
/DN Port 6 (5A)/VBUS_CONN: C153.1, FB7.2, J7.A4 (VBUS), J7.A9 (VBUS), J7.B4 (VBUS), J7.B9 (VBUS), R85.1
/DN Port 6 (5A)/VBUS_DET: R85.2, U42.5 (VBUS_DET)
/DN Port 6 (5A)/VBUS_SW: C156.2, C157.1, C158.1, FB7.1, R88.2, R139.1, U45.8 (Vbus), U45.9 (Vin-)
/I2C0_SCL: U45.1 (A1), U45.2 (A0), U45.5 (SCL); also elsewhere on the board
/I2C0_SDA: U45.4 (SDA); also elsewhere on the board
/MUX_DISABLE: U42.29 (ENn_CC); also elsewhere on the board
/TUSB8044A Hub1/PWRON3_BATEN3: R81.1; also elsewhere on the board
/USB6_INHIBIT: R150.1; also elsewhere on the board
/USBLED_56: R89.2; also elsewhere on the board
GND: C146.2, C147.2, C148.2, C153.2, C154.2, C155.2, C157.2, C158.2, C159.2, J7.A1 (GND), J7.A12 (GND), J7.B1 (GND), J7.B12 (GND), J7.SH (SHIELD), Q6.2 (S), Q19.2 (S), R87.2, R139.2, R151.2, U40.3 (GND), U40.8 (GND), U41.3 (GND), U41.8 (GND), U42.12 (ENn_MUX), U42.13 (GND), U42.28 (GND), U42.31 (PAD), U43.3 (GND), U43.8 (GND), U44.1 (GND), U44.9 (PAD), U45.7 (GND); also elsewhere on the board
unnamed: D7.1 (K), R89.1
unnamed: Q19.1 (G), R150.2, R151.1
unnamed: R87.1, U44.5 (ILIM)

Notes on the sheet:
VBUS FILTER
I2C address is strapped on the root through ADDR_A1 / ADDR_A0.
STRAPS AND PULL-UPS
polarity swap is detected in the receiver
R_ILIM 20K: limit 5.18 A min / 5.54 A typ / 5.80 A max (datasheet eq. 1).
CC CONTROLLER + SS MUX (DFP, GPIO mode)
R102 sets Type-C current advertisement: NOPOP = default, 499K = 1.5A, 10K = 3A
PORT POWER SWITCH (per TUSB8044AEVM)
CUR_MODE 10K fitted = 3 A Type-C advertisement (max without USB-PD).
SS TX AC COUPLING (place at connector)
PORT 6 POWER: R81 DNI; R171 (100k, +3V3 to SW_EN) fitted. Power follows attach detection independently of hub PWRON. USB_INHIBIT remains effective for firmware shutdown. Fit only one of R81/R171; swap population to restore hub power control.
SHIELD TERMINATION
Pi 5 draws >3 A only with PSU_MAX_CURRENT=5000 or usb_max_current_enable=1 set on the Pi.
ESD PROTECTION
USB-C DOWNSTREAM PORT MODULE
PORT CURRENT MONITOR: INA226 across 5 mOhm in VBUS, after the switch.
5 A VARIANT of usbc_dfp (full USB 3 data). TPS2557: 25 mOhm, EN active high, 5 A continuous.
USB_INHIBIT high forces VBUS off. Low / MCU reset permits normal hub and attach control. Place the inhibit FET and gate pulldown near the power switch. Gate resistors: 0402.
VBUS ATTACH GATE

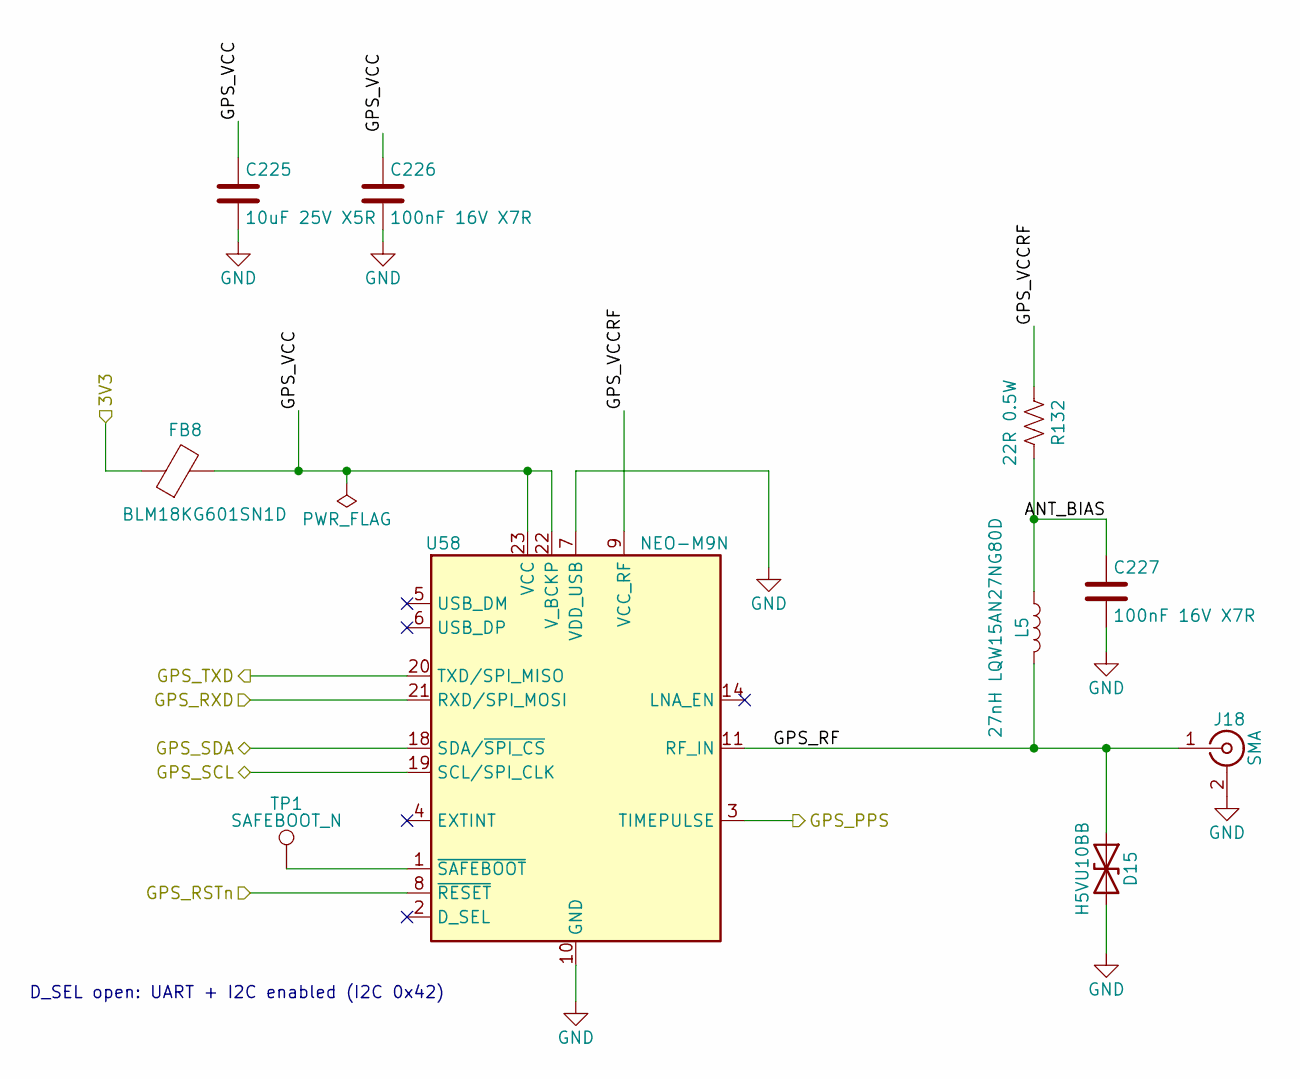
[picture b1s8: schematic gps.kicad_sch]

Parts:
C225: 10uF 25V X5R; C_0805_2012Metric; LCSC C15850
C226, C227: 100nF 16V X7R; C_0402_1005Metric; LCSC C1525
D15: H5VU10BB; D_0402_1005Metric; LCSC C20615786
FB8: BLM18KG601SN1D; L_0603_1608Metric; LCSC C85833
J18: SMA; SMA_Molex_73251-1153_EdgeMount_Horizontal
L5: 27nH LQW15AN27NG80D; L_0402_1005Metric; LCSC C882469
R132: 22R 0.5W; R_1206_3216Metric; LCSC C2845146
TP1: SAFEBOOT_N; TestPoint_Pad_D1.0mm
U58: NEO-M9N; ublox_NEO; LCSC C5119087

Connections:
+3V3: FB8.1; also elsewhere on the board
/GPS/ANT_BIAS: C227.1, L5.1, R132.2
/GPS/GPS_RF: D15.1 (A1), J18.1 (In), L5.2, U58.11 (RF_IN)
/GPS/GPS_VCC: C225.1, C226.1, FB8.2, U58.22 (V_BCKP), U58.23 (VCC)
/GPS/GPS_VCCRF: R132.1, U58.9 (VCC_RF)
/GPS_PPS: U58.3 (TIMEPULSE); also elsewhere on the board
/GPS_RSTn: U58.8 (~RESET); also elsewhere on the board
/GPS_RXD: U58.21 (RXD/SPI_MOSI); also elsewhere on the board
/GPS_TXD: U58.20 (TXD/SPI_MISO); also elsewhere on the board
/I2C1_SCL: U58.19 (SCL/SPI_CLK); also elsewhere on the board
/I2C1_SDA: U58.18 (SDA/~SPI_CS); also elsewhere on the board
GND: C225.2, C226.2, C227.2, D15.2 (A2), J18.2 (Ext), U58.7 (VDD_USB), U58.10 (GND), U58.12 (GND), U58.13 (GND), U58.24 (GND); also elsewhere on the board
unnamed: TP1.1 (1_1), U58.1 (~SAFEBOOT)

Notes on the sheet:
D_SEL open: UART + I2C enabled (I2C 0x42)
